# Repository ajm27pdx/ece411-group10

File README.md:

# ECE411 Group 10 - 2022 Fall Practicum Project

## Members
* Jing Ma
* Adam Martinez
* Janvier Mpfizi
* Tysen Tippetts
## Product Design Specifications
[>>HERE<<](PDS/PDS.md)
## Funcitonal Decomposition
### L0

### L1

## Bill of Materials
[Google Sheets Link](https://docs.google.com/spreadsheets/d/1Y6daa6rxvxdisMLShwMxon2ES7SXVknLk-44MzFfnI0/edit?usp=sharing)
### Controllers
- Arduino Uno
### Sensors
- Photoresistors
- RFID Sensor RC522
- Button
### Actuators
- Servo Motor SG90
- LED Lasor 6mm 5mW Red Dot Laser
- LCD Screen 1602 w/ I2C controller
### Misc
- Wires
- RFID Fob
- Resistors
- 3D Printed Enclosure

## Software
- [KiCAD](https://www.kicad.org/) -- Schematic and PCB Layout
- [FreeCAD](https://www.freecadweb.org/) -- 3D Modeling
- [ProjectLibre](https://www.projectlibre.com/) -- Project Management

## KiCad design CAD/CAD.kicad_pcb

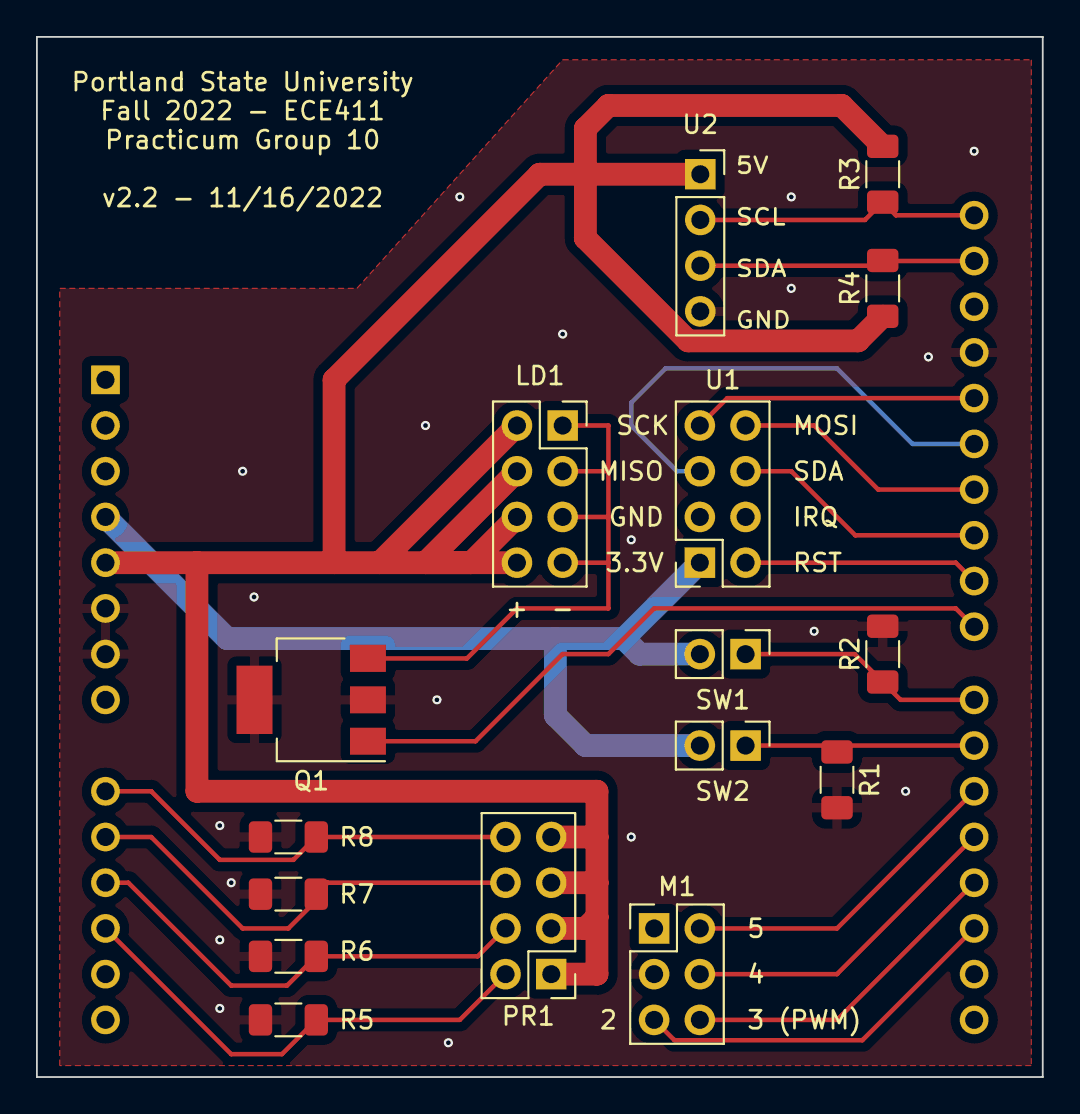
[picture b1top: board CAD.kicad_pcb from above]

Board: 2 copper layers, 55.9 x 57.8 mm, 17 parts (1 on the bottom side), 22 nets.

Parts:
A1: Arduino_UNO_R3
LD1: D_Laser_1C2A; PinSocket_2x04_P2.54mm_Vertical
M1: Motor_Servo_Hitec; PinHeader_2x03_P2.54mm_Vertical
PR1: R_Photo; PinHeader_2x04_P2.54mm_Vertical
Q1: 2N7002; SOT-223-3_TabPin2
R1, R2, R5, R6, R7, R8: 10k; R_1206_3216Metric_Pad1.30x1.75mm_HandSolder
R3, R4: 4.7k; R_1206_3216Metric_Pad1.30x1.75mm_HandSolder
SW1, SW2: SW_Push; PinHeader_1x02_P2.54mm_Vertical
U1: RFID_RC522; PinSocket_2x04_P2.54mm_Vertical
U2: LCD_1602_I2C; PinSocket_1x04_P2.54mm_Vertical

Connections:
+3.3V: A1.4 (3V3), SW1.2, SW2.2, U1.1 (3.3V)
+5V: A1.5 (+5V), LD1.2 (A), LD1.4, LD1.6, LD1.8, PR1.1, PR1.3, PR1.5, PR1.7, R3.2, R4.1, U2.1 (VCC)
GND: A1.6 (GND), A1.7 (GND), A1.29 (GND), M1.3 (-), Q1.2 (S), R1.2, R2.2, R5.2, R6.2, R7.2, R8.2, U2.4 (GND)
unnamed: A1.9 (A0), PR1.8, R8.1
unnamed: A1.10 (A1), PR1.6, R7.1
unnamed: A1.11 (A2), PR1.4, R6.1
unnamed: A1.12 (A3), PR1.2, R5.1
unnamed: A1.17 (D2), M1.5
unnamed: A1.18 (D3), M1.6
unnamed: A1.19 (D4), M1.4
unnamed: A1.20 (D5), M1.2 (PWM)
unnamed: A1.21 (D6), R1.1, SW2.1
unnamed: A1.22 (D7), R2.1, SW1.1
unnamed: A1.23 (D8), Q1.1 (G)
unnamed: A1.24 (D9), U1.2 (RST)
unnamed: A1.25 (D10), U1.6 (SDA)
unnamed: A1.26 (D11), U1.8 (MOSI)
unnamed: A1.27 (D12), U1.5 (MISO)
unnamed: A1.28 (D13), U1.7 (SLK)
unnamed: A1.31 (SDA/A4), R4.2, U2.3 (SDA)
unnamed: A1.32 (SCL/A5), R3.1, U2.2 (SCL)
unnamed: LD1.1 (K), LD1.3, LD1.5, LD1.7, Q1.3 (D)

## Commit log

2022-11-02 Added first pass proj management, updated readme
2022-11-03 Added prototype demo
2022-11-03 added pcb layout v0.1
2022-11-03 Adjusted dates on schedule
2022-11-10 updated pcb layout with template
2022-11-10 added BOM
2022-11-10 Fixed pcb footprints, passing DRC!
2022-11-10 updated decomp diagrams
2022-11-10 updated README with new links
2022-11-17 Final CAD
2022-11-17 Added dirs to code
2022-12-04 Added test plans
2022-12-04 added initial code dump
2022-12-07 added stl files
2022-12-08 final version of stl files
2022-12-08 code revision
